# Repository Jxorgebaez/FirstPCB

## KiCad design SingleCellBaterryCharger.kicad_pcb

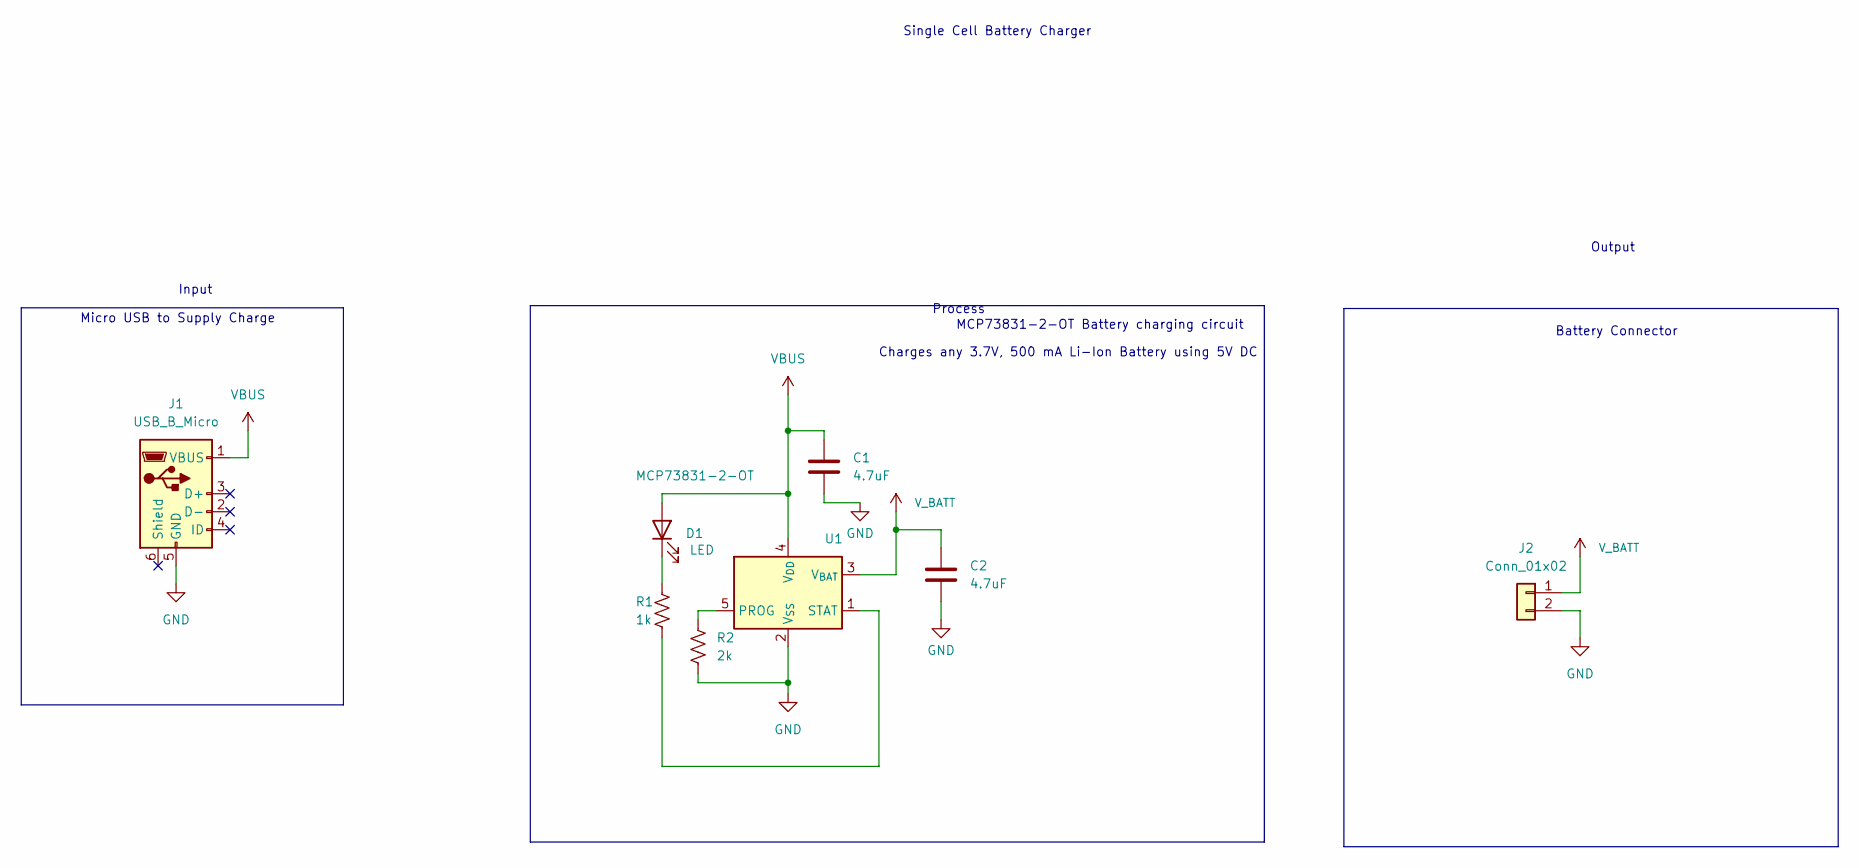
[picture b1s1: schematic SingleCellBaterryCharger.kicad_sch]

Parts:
C1, C2: 4.7uF; C_1206_3216Metric_Pad1.33x1.80mm_HandSolder
D1: LED; LED_1206_3216Metric_Pad1.42x1.75mm_HandSolder
J1: USB_B_Micro; USB_Micro-B_Molex-105017-0001
J2: Conn_01x02; JST_GH_SM02B-GHS-TB_1x02-1MP_P1.25mm_Horizontal
R1: 1k; R_1206_3216Metric_Pad1.30x1.75mm_HandSolder
R2: 2k; R_1206_3216Metric_Pad1.30x1.75mm_HandSolder
U1: MCP73831-2-OT; SOT-23-5

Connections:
GND: C1.2, C2.2, J1.5 (GND), J2.2, R2.2, U1.2 (V_{SS})
unnamed: D1.1 (K), R1.1
unnamed: R2.1, U1.5 (PROG)
unnamed: R1.2, U1.1 (STAT)
VBUS: C1.1, D1.2 (A), J1.1 (VBUS), U1.4 (V_{DD})
V_BATT: C2.1, J2.1, U1.3 (V_{BAT})

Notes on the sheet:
Output
Charges any 3.7V, 500 mA Li-Ion Battery using 5V DC
Input
Battery Connector
MCP73831-2-OT Battery charging circuit
Process
Micro USB to Supply Charge
Single Cell Battery Charger

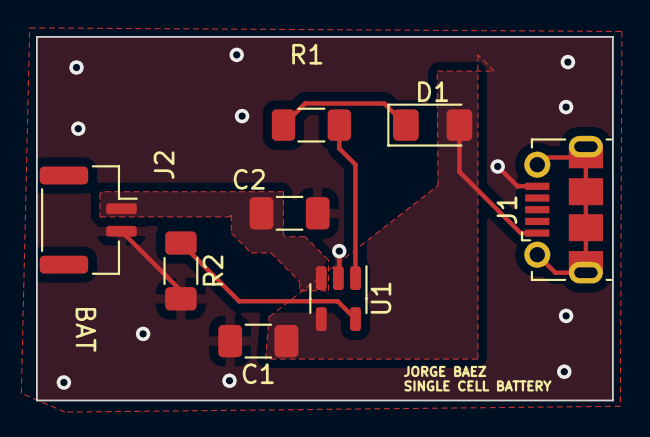
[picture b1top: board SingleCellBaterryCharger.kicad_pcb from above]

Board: 2 copper layers, 32.0 x 20.2 mm, 8 parts (0 on the bottom side), 6 nets.

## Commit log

2023-08-02 Added project files
